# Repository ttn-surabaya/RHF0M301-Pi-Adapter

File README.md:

# RisingHF RHF0M301 - Raspberry Pi Adapter

This is a simple adapter / backplane for RisingHF RHF0M301 LoRa Gateway and Raspberry Pi 2/3. 

More info about [**RHF0M301 LoRa Gateway**](http://www.risinghf.com/product/rhf0m301/?lang=en)<br>

## Configuration

The following pin configuration is used on this board (v1.1)

RHF0M301 pin    | Description   | RPi physical pin
----------------|---------------|-----------------
1,2             | Supply 5V     | 2
3,4,21,22,23    | GND           | 6
14              | Reset         | 22
16              | SPI CLK       | 23
15              | SPI MISO      | 21
18              | SPI MOSI      | 19
17              | SPI NSS       | 24

There is a jumper select pin to change the RHF0301 power source from either Rpi 5V or External 5V. You also could add GPS (UBlox Neo M6/M7/M8) on this board or just leave it empty.

## LoRa Packet Forwarder Installation

There are a couple of packet forwarder software libraries that you could use for this RPI - RHF0M301 LoRa Gateway for example:
* [**The Things Network Packet Forwarder**](https://github.com/TheThingsNetwork/packet_forwarder)<br>
* [**Official RisingHF Packet Forwarder**](https://github.com/risinghf/packet_forwarder)<br>
* [**Resin IO / TTN Packet Forwarder**](https://github.com/jpmeijers/ttn-resin-gateway-rpi)<br>

As you might notice, the RHF0M301 uses similar hardware as in other gateways such as IMST ic880a which is based on Semtech SX1301. The software is pretty much the same but usually they vary in pinout (i.e. Reset Pin).

If you wish to use this gateway for The Things Networks Environment, then I suggest you to follow the [**IMST ic880a Instruction at TTN Official Github page**](https://github.com/TheThingsNetwork/packet_forwarder/blob/master/docs/INSTALL_INSTRUCTIONS/IMST_RPI.md)<br>.
It will work straight away as the wiring configuration is identical.

## Revision History
* v1.0 Initial Design
* v1.1 Changed Reset Pin to Pin 22, added filter circuit on reset line, changed caps on 5V power line.

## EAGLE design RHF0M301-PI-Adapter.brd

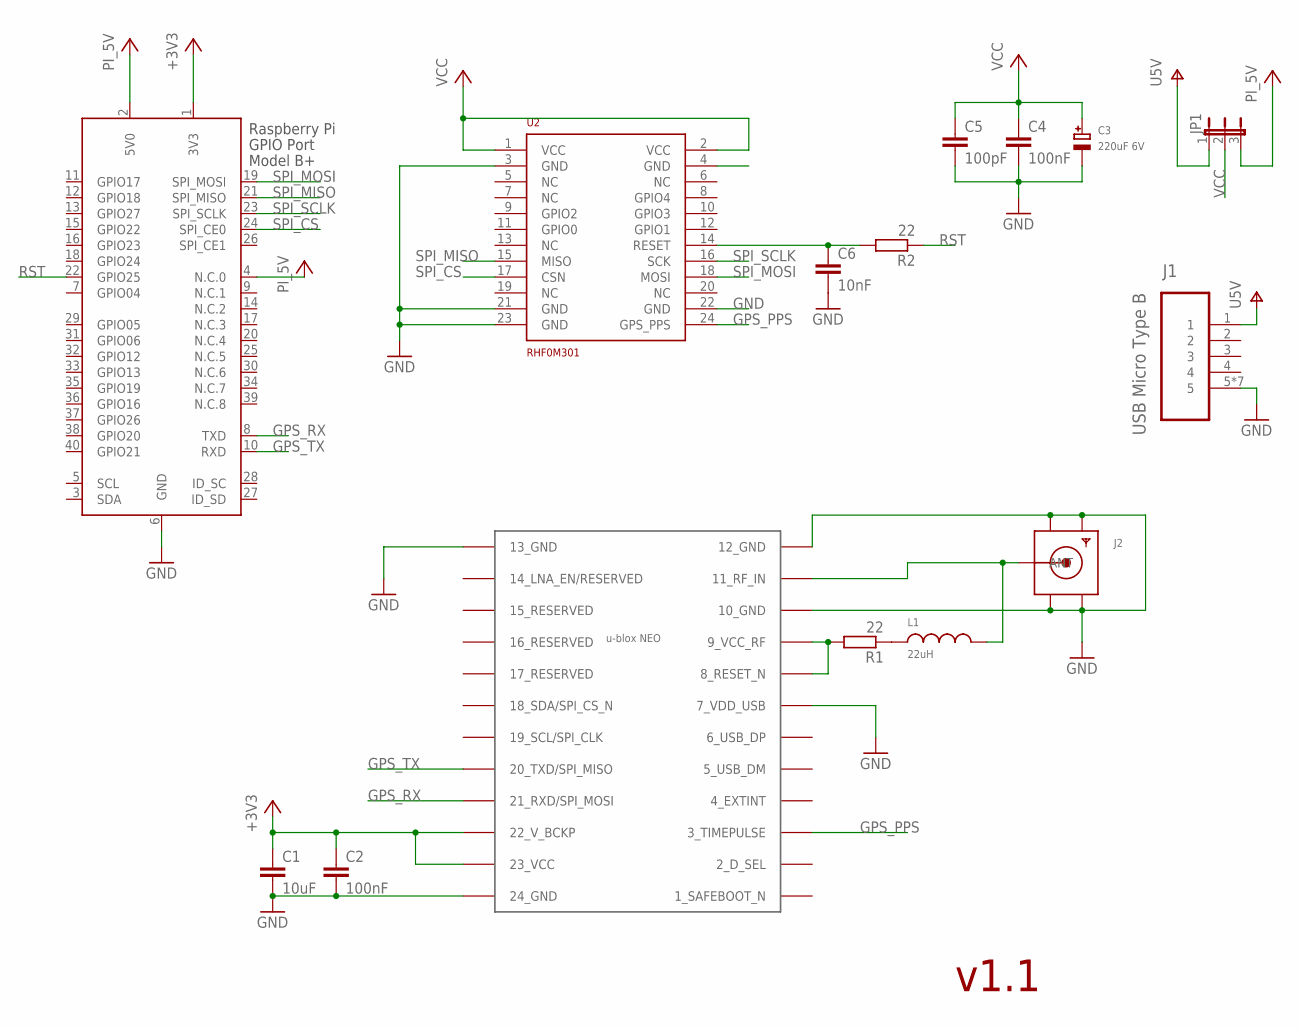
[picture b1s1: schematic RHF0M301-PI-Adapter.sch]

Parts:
C1: 10uF; 0805_MP
C2, C4: 100nF; 0603_MP
C3: 220uF 6V; EIA6032-28/C-R
C5: 100pF; 0603_MP
C6: 10nF; 0603_MP
J1: USB Micro Type B; MOLEX_47346-0001
J2: MICROBUILDER_SMACONNECTOR_EDGE_UFL; MICROBUILDER_SMA_EDGELAUNCH_UFL
JP1: JUMPER3
L1: 22uH; R0805
R1, R2: 22; 0603_MP
U1: NEO-M8
U2: RHF0M301; RFM0M301
X2: RASPI_BOARD_B+_H; RASPI_BOARD_B+HAT

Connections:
+3V3: C1.1, C2.1, U1.22 (22_V_BCKP), U1.23 (23_VCC), X2.1 (3V3)
+5V: JP1.3, X2.2 (5V0), X2.4 (N.C.0)
GND: C1.2, C2.2, C3.-, C4.2, C5.2, C6.2, J1.5, J1.M1 (5), J1.M2 (5), J1.M3 (5), J1.M4 (5), J1.M5 (5), J1.M6 (5), J2.GND@1 (GND1), J2.GND@2 (GND2), J2.GND@3 (GND3), J2.GND@4 (GND4), U1.7 (7_VDD_USB), U1.10 (10_GND), U1.12 (12_GND), U1.13 (13_GND), U1.24 (24_GND), U2.3 (GND), U2.4 (GND), U2.21 (GND), U2.22 (GND), U2.23 (GND), X2.6 (GND)
GPS_PPS: U1.3 (3_TIMEPULSE), U2.24 (GPS_PPS)
GPS_RX: U1.21 (21_RXD/SPI_MOSI), X2.8 (TXD)
GPS_TX: U1.20 (20_TXD/SPI_MISO), X2.10 (RXD)
unnamed: C6.1, R2.2, U2.14 (RESET)
unnamed: L1.1, R1.1
unnamed: J2.P (ANT), L1.2, U1.11 (11_RF_IN)
unnamed: R1.2, U1.8 (8_RESET_N), U1.9 (9_VCC_RF)
RST: R2.1, X2.22 (GPIO25)
SPI_CS: U2.17 (CSN), X2.24 (SPI_CE0)
SPI_MISO: U2.15 (MISO), X2.21 (SPI_MISO)
SPI_MOSI: U2.18 (MOSI), X2.19 (SPI_MOSI)
SPI_SCLK: U2.16 (SCK), X2.23 (SPI_SCLK)
V+: J1.1, JP1.1
VCC: C3.+, C4.1, C5.1, JP1.2, U2.1 (VCC), U2.2 (VCC)

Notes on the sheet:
v1.1

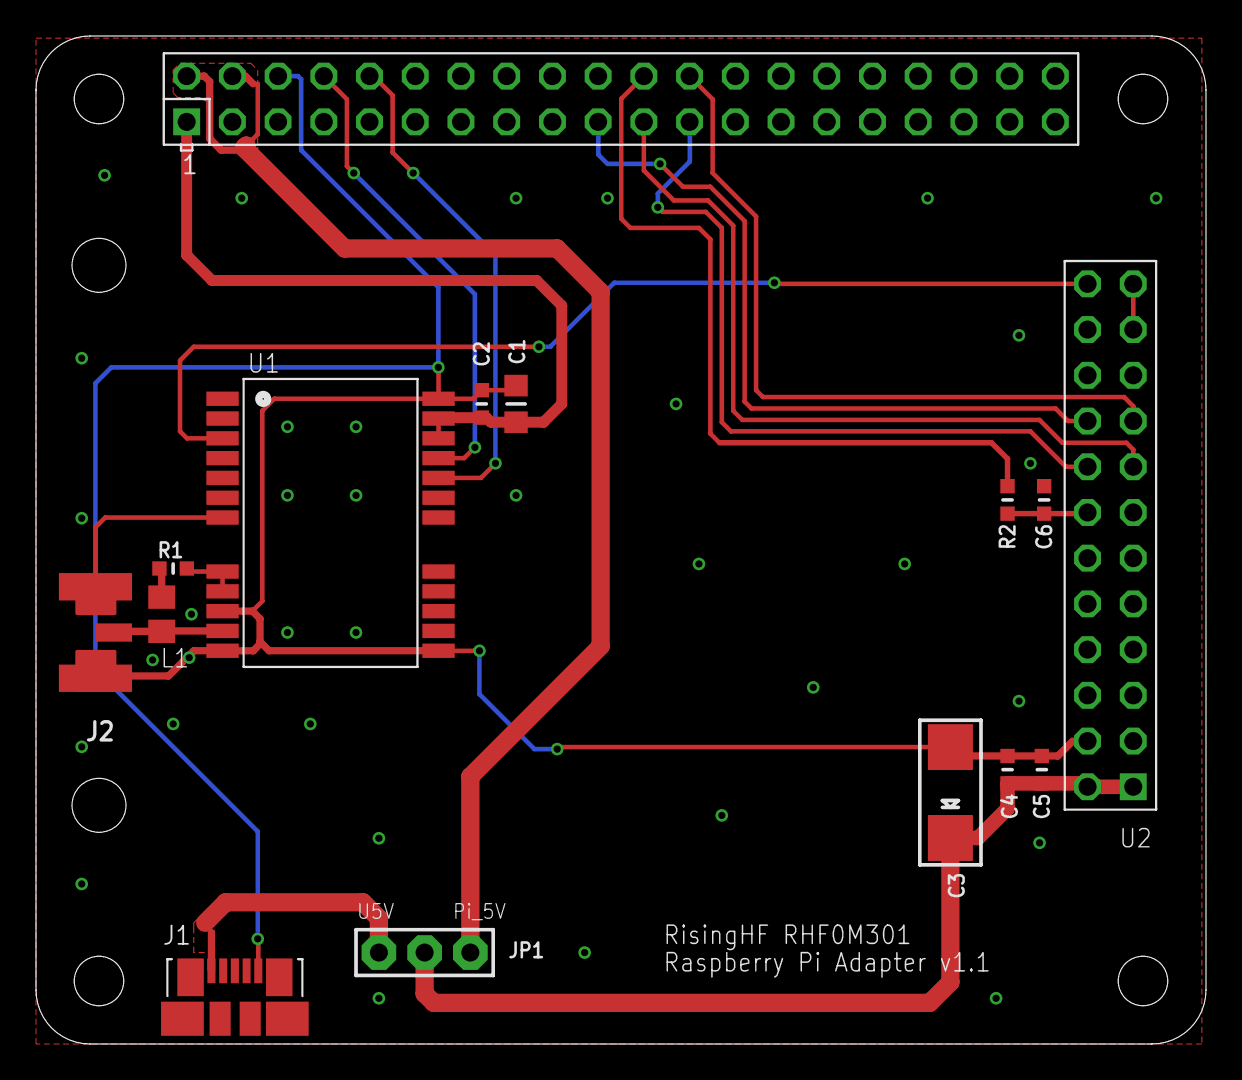
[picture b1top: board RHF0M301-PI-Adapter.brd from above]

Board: 2 copper layers, 65.0 x 56.0 mm, 15 parts (0 on the bottom side), 17 nets.

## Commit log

2017-07-01 fix readme
2017-07-18 Edit Licence
2017-07-20 added images to the repository
2017-07-21 Fix --reset-pin command
2018-06-08 updated v1.1
2018-06-08 Update info on v1.1 Revision

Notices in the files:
parts and their libraries:
microbuilder: This work is placed in the public domain, and may be freely used for commercial and non-commercial work with the following conditions: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
